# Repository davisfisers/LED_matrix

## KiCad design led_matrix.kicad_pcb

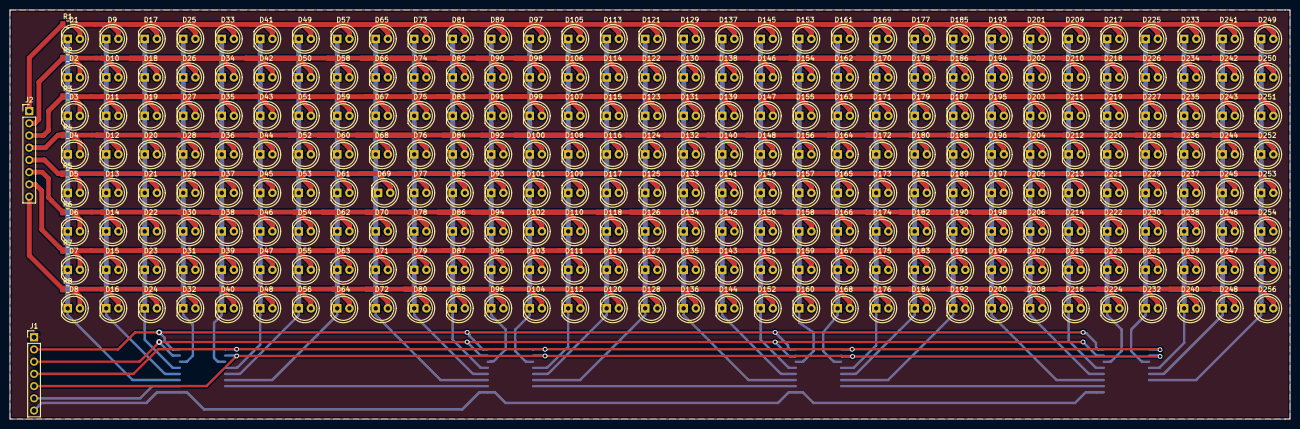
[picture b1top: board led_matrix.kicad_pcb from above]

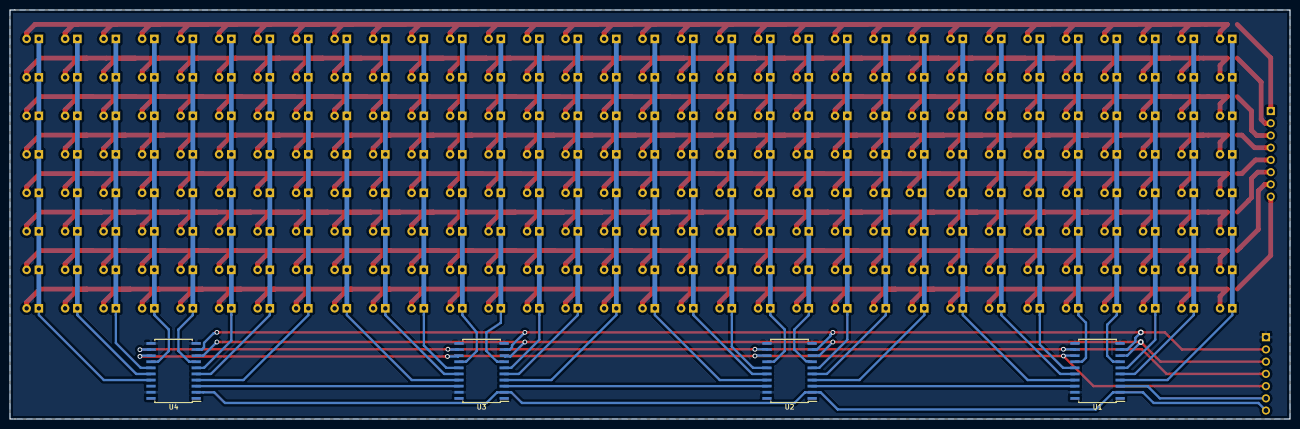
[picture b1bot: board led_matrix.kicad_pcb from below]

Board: 2 copper layers, 266.0 x 85.0 mm, 270 parts (4 on the bottom side), 58 nets.

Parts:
D1, D2, D3, D4, D5, D6, D7, D8, D9, D10, D11, D12, D13, D14, D15, D16, D17, D18, D19, D20, D21, D22, D23, D24, D25, D26, D27, D28, D29, D30, D31, D32, D33, D34, D35, D36, D37, D38, D39, D40, D41, D42, D43, D44, D45, D46, D47, D48, D49, D50, D51, D52, D53, D54, D55, D56, D57, D58, D59, D60, D61, D62, D63, D64, D65, D66, D67, D68, D69, D70, D71, D72, D73, D74, D75, D76, D77, D78, D79, D80, D81, D82, D83, D84, D85, D86, D87, D88, D89, D90, D91, D92, D93, D94, D95, D96, D97, D98, D99, D100, D101, D102, D103, D104, D105, D106, D107, D108, D109, D110, D111, D112, D113, D114, D115, D116, D117, D118, D119, D120, D121, D122, D123, D124, D125, D126, D127, D128, D129, D130, D131, D132, D133, D134, D135, D136, D137, D138, D139, D140, D141, D142, D143, D144, D145, D146, D147, D148, D149, D150, D151, D152, D153, D154, D155, D156, D157, D158, D159, D160, D161, D162, D163, D164, D165, D166, D167, D168, D169, D170, D171, D172, D173, D174, D175, D176, D177, D178, D179, D180, D181, D182, D183, D184, D185, D186, D187, D188, D189, D190, D191, D192, D193, D194, D195, D196, D197, D198, D199, D200, D201, D202, D203, D204, D205, D206, D207, D208, D209, D210, D211, D212, D213, D214, D215, D216, D217, D218, D219, D220, D221, D222, D223, D224, D225, D226, D227, D228, D229, D230, D231, D232, D233, D234, D235, D236, D237, D238, D239, D240, D241, D242, D243, D244, D245, D246, D247, D248, D249, D250, D251, D252, D253, D254, D255, D256: LED; LED_D5.0mm
J1: Conn_01x07; PinHeader_1x07_P2.54mm_Vertical
J2: Conn_01x08; PinHeader_1x08_P2.54mm_Vertical
R1, R2, R3, R4, R5, R6, R7, R8: 45k; R_0805_2012Metric_Pad1.15x1.40mm_HandSolder
U1, U2, U3, U4: TPIC6B595; SOIC-20W_7.5x12.8mm_P1.27mm

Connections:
GND: J1.1, U1.10, U1.11, U1.19, U2.10, U2.11, U2.19, U3.10, U3.11, U3.19, U4.10, U4.11, U4.19
unnamed: D1.1, D2.1, D3.1, D4.1, D5.1, D6.1, D7.1, D8.1, U1.4
unnamed: D1.2, D9.2, D17.2, D25.2, D33.2, D41.2, D49.2, D57.2, D65.2, D73.2, D81.2, D89.2, D97.2, D105.2, D113.2, D121.2, D129.2, D137.2, D145.2, D153.2, D161.2, D169.2, D177.2, D185.2, D193.2, D201.2, D209.2, D217.2, D225.2, D233.2, D241.2, D249.2, R1.2
unnamed: D9.1, D10.1, D11.1, D12.1, D13.1, D14.1, D15.1, D16.1, U1.5
unnamed: D2.2, D10.2, D18.2, D26.2, D34.2, D42.2, D50.2, D58.2, D66.2, D74.2, D82.2, D90.2, D98.2, D106.2, D114.2, D122.2, D130.2, D138.2, D146.2, D154.2, D162.2, D170.2, D178.2, D186.2, D194.2, D202.2, D210.2, D218.2, D226.2, D234.2, D242.2, D250.2, R2.2
unnamed: D17.1, D18.1, D19.1, D20.1, D21.1, D22.1, D23.1, D24.1, U1.6
unnamed: D25.1, D26.1, D27.1, D28.1, D29.1, D30.1, D31.1, D32.1, U1.7
unnamed: D33.1, D34.1, D35.1, D36.1, D37.1, D38.1, D39.1, D40.1, U1.14
unnamed: D41.1, D42.1, D43.1, D44.1, D45.1, D46.1, D47.1, D48.1, U1.15
unnamed: D49.1, D50.1, D51.1, D52.1, D53.1, D54.1, D55.1, D56.1, U1.16
unnamed: D57.1, D58.1, D59.1, D60.1, D61.1, D62.1, D63.1, D64.1, U1.17
unnamed: D65.1, D66.1, D67.1, D68.1, D69.1, D70.1, D71.1, D72.1, U2.4
unnamed: D73.1, D74.1, D75.1, D76.1, D77.1, D78.1, D79.1, D80.1, U2.5
unnamed: D81.1, D82.1, D83.1, D84.1, D85.1, D86.1, D87.1, D88.1, U2.6
unnamed: D89.1, D90.1, D91.1, D92.1, D93.1, D94.1, D95.1, D96.1, U2.7
unnamed: D97.1, D98.1, D99.1, D100.1, D101.1, D102.1, D103.1, D104.1, U2.14
unnamed: D4.2, D12.2, D20.2, D28.2, D36.2, D44.2, D52.2, D60.2, D68.2, D76.2, D84.2, D92.2, D100.2, D108.2, D116.2, D124.2, D132.2, D140.2, D148.2, D156.2, D164.2, D172.2, D180.2, D188.2, D196.2, D204.2, D212.2, D220.2, D228.2, D236.2, D244.2, D252.2, R4.2
unnamed: D5.2, D13.2, D21.2, D29.2, D37.2, D45.2, D53.2, D61.2, D69.2, D77.2, D85.2, D93.2, D101.2, D109.2, D117.2, D125.2, D133.2, D141.2, D149.2, D157.2, D165.2, D173.2, D181.2, D189.2, D197.2, D205.2, D213.2, D221.2, D229.2, D237.2, D245.2, D253.2, R5.2
unnamed: D6.2, D14.2, D22.2, D30.2, D38.2, D46.2, D54.2, D62.2, D70.2, D78.2, D86.2, D94.2, D102.2, D110.2, D118.2, D126.2, D134.2, D142.2, D150.2, D158.2, D166.2, D174.2, D182.2, D190.2, D198.2, D206.2, D214.2, D222.2, D230.2, D238.2, D246.2, D254.2, R6.2
unnamed: D7.2, D15.2, D23.2, D31.2, D39.2, D47.2, D55.2, D63.2, D71.2, D79.2, D87.2, D95.2, D103.2, D111.2, D119.2, D127.2, D135.2, D143.2, D151.2, D159.2, D167.2, D175.2, D183.2, D191.2, D199.2, D207.2, D215.2, D223.2, D231.2, D239.2, D247.2, D255.2, R7.2
unnamed: D8.2, D16.2, D24.2, D32.2, D40.2, D48.2, D56.2, D64.2, D72.2, D80.2, D88.2, D96.2, D104.2, D112.2, D120.2, D128.2, D136.2, D144.2, D152.2, D160.2, D168.2, D176.2, D184.2, D192.2, D200.2, D208.2, D216.2, D224.2, D232.2, D240.2, D248.2, D256.2, R8.2
unnamed: D105.1, D106.1, D107.1, D108.1, D109.1, D110.1, D111.1, D112.1, U2.15
unnamed: D3.2, D11.2, D19.2, D27.2, D35.2, D43.2, D51.2, D59.2, D67.2, D75.2, D83.2, D91.2, D99.2, D107.2, D115.2, D123.2, D131.2, D139.2, D147.2, D155.2, D163.2, D171.2, D179.2, D187.2, D195.2, D203.2, D211.2, D219.2, D227.2, D235.2, D243.2, D251.2, R3.2
unnamed: D113.1, D114.1, D115.1, D116.1, D117.1, D118.1, D119.1, D120.1, U2.16
unnamed: D121.1, D122.1, D123.1, D124.1, D125.1, D126.1, D127.1, D128.1, U2.17
unnamed: D129.1, D130.1, D131.1, D132.1, D133.1, D134.1, D135.1, D136.1, U3.4
unnamed: D137.1, D138.1, D139.1, D140.1, D141.1, D142.1, D143.1, D144.1, U3.5
unnamed: D145.1, D146.1, D147.1, D148.1, D149.1, D150.1, D151.1, D152.1, U3.6
unnamed: D153.1, D154.1, D155.1, D156.1, D157.1, D158.1, D159.1, D160.1, U3.7
unnamed: D161.1, D162.1, D163.1, D164.1, D165.1, D166.1, D167.1, D168.1, U3.14
unnamed: D169.1, D170.1, D171.1, D172.1, D173.1, D174.1, D175.1, D176.1, U3.15
unnamed: D177.1, D178.1, D179.1, D180.1, D181.1, D182.1, D183.1, D184.1, U3.16
unnamed: D185.1, D186.1, D187.1, D188.1, D189.1, D190.1, D191.1, D192.1, U3.17
unnamed: D193.1, D194.1, D195.1, D196.1, D197.1, D198.1, D199.1, D200.1, U4.4
unnamed: D201.1, D202.1, D203.1, D204.1, D205.1, D206.1, D207.1, D208.1, U4.5
unnamed: D209.1, D210.1, D211.1, D212.1, D213.1, D214.1, D215.1, D216.1, U4.6
unnamed: D217.1, D218.1, D219.1, D220.1, D221.1, D222.1, D223.1, D224.1, U4.7
unnamed: D225.1, D226.1, D227.1, D228.1, D229.1, D230.1, D231.1, D232.1, U4.14
unnamed: D233.1, D234.1, D235.1, D236.1, D237.1, D238.1, D239.1, D240.1, U4.15
unnamed: D241.1, D242.1, D243.1, D244.1, D245.1, D246.1, D247.1, D248.1, U4.16
unnamed: D249.1, D250.1, D251.1, D252.1, D253.1, D254.1, D255.1, D256.1, U4.17
unnamed: J1.2, U1.9, U2.9, U3.9, U4.9
unnamed: J1.3, U1.8, U2.8, U3.8, U4.8
unnamed: J1.4, U1.12, U2.12, U3.12, U4.12
unnamed: J1.5, U1.13, U2.13, U3.13, U4.13
unnamed: J1.6, U1.3
unnamed: J1.7, U1.2, U2.2, U3.2, U4.2
unnamed: J2.1, R1.1
unnamed: J2.2, R2.1
unnamed: J2.3, R3.1
unnamed: J2.4, R4.1
unnamed: J2.5, R5.1
unnamed: J2.6, R6.1
unnamed: J2.7, R7.1
unnamed: J2.8, R8.1
unnamed: U1.18, U2.3
unnamed: U2.18, U3.3
unnamed: U3.18, U4.3

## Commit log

2019-03-23 upload
